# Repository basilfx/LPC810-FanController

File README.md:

# LPC810 Fan Controller
Tiny PID-based fan controller board and firmware, to insert between 3-pin fans.

## Contents
* Eagle schematic and PCB
* Firmware
* PID simulator and monitor

## Eagle

### Bill of Materials
The value of is a pullup resistor for the DS18B20 temperature sensor. While 4.7k is adviced, I use 470 in parasite mode. Higher values did not work for higher temperatures.

| Part | Value  | Device          | Package |
|------|--------|-----------------|---------|
| R1   | 470    | R-EU_R0603      | R0603   |
| R2   | 10k    | R-EU_R0603      | R0603   |
| R3   | 10k    | R-EU_R0603      | R0603   |
| R4   | 10k    | R-EU_R0603      | R0603   |
| C1   | 100nF  | C-EUC0603       | C0603   |
| C2   | 2.2µF  | C-EUC0805       | C0805   |
| C3   | 100nF  | C-EUC0603       | C0603   |
| C4   | 2.2µF  | C-EUC0805       | C0805   |
| Q1   | BSH103 | MOSFET-NCHANNEL | SOT23   |
| U1   | LP2985 | LP2985-33DBVT   | SOT95P  |
| U2   | LPC810 | LPC810M021FN8   | DIP8    |

### Board render
The board measures 0.45x0.95 inch. Below a render of the top and bottom.

## Firmware
The firmware can be found in the `firmware/` folder. It compiles fine with the [GCC ARM Embedded](https://launchpad.net/gcc-arm-embedded) toolchain. Just run `make`.

## Contrib
In the `contrib` folder contains some tools to test the PID controller. First, run `python setup.py build_ext --inplace` to build a Python wrapper for the exact same PID controller in the firmware. This requires Cython to be available.

## License
See the `LICENSE` file (MIT license).

This software makes use of other software. Please see `firmware/README.md` for more information.

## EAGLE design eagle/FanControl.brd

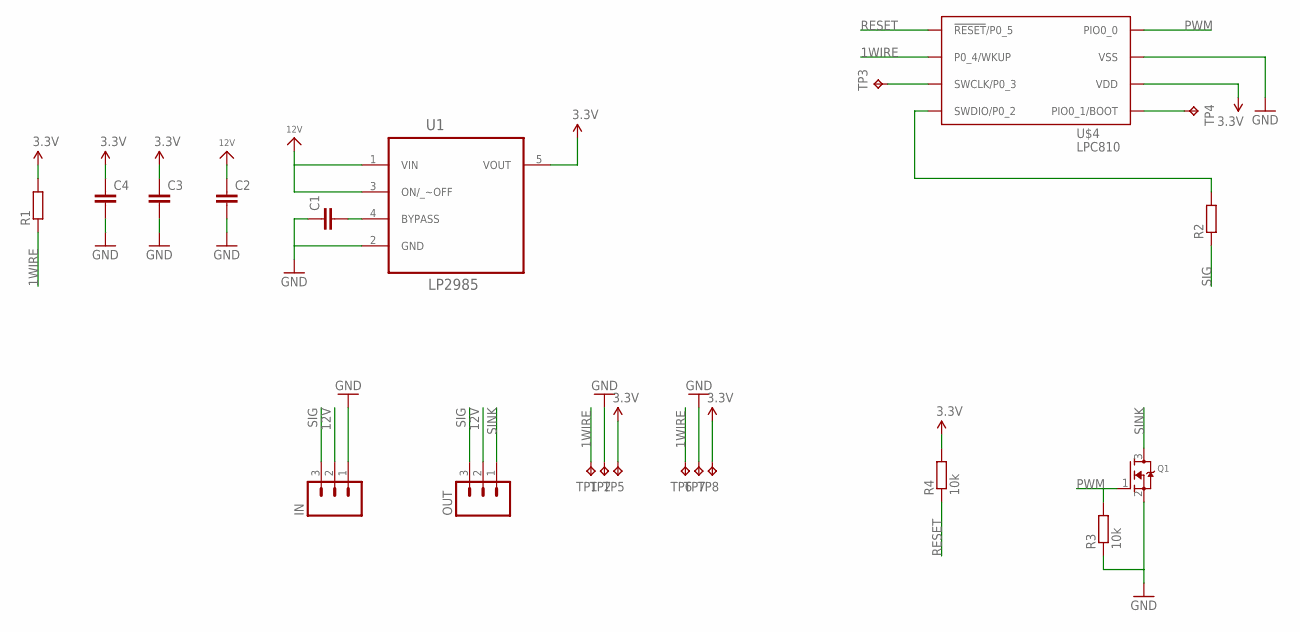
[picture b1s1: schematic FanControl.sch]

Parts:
C1, C3: C-EUC0603; C0603
C2, C4: C-EUC0805; C0805
IN: M03PTH; 1X03
OUT: M03PTH; 1X03
Q1: MOSFET-NREFLOW; SOT23
R1, R2: R-EU_R0603; R0603
R3, R4: 10k; R0603
TP1, TP2, TP3, TP4, TP5, TP6, TP7, TP8: TPB1,27; B1,27
U1: LP2985; SOT95P280X145-5N
U$4: LPC810; DIP8

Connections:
1WIRE: R1.1, TP1.TP, TP6.TP, U$4.P$2 (P0_4/WKUP)
3.3V: C3.1, C4.1, R1.2, R4.2, TP5.TP, TP8.TP, U1.5 (VOUT), U$4.P$6 (VDD)
12V: C2.1, IN.2, OUT.2, U1.1 (VIN), U1.3 (ON/_~OFF)
GND: C1.1, C2.2, C3.2, C4.2, IN.1, Q1.2 (S), R3.1, TP2.TP, TP7.TP, U1.2 (GND), U$4.P$7 (VSS)
unnamed: C1.2, U1.4 (BYPASS)
unnamed: R2.2, U$4.P$4 (SWDIO/P0_2)
unnamed: TP3.TP, U$4.P$3 (SWCLK/P0_3)
unnamed: TP4.TP, U$4.P$5 (PIO0_1/BOOT)
PWM: Q1.1 (G), R3.2, U$4.P$8 (PIO0_0)
RESET: R4.1, U$4.P$1 (!RESET!/P0_5)
SIG: IN.3, OUT.3, R2.1
SINK: OUT.1, Q1.3 (D)

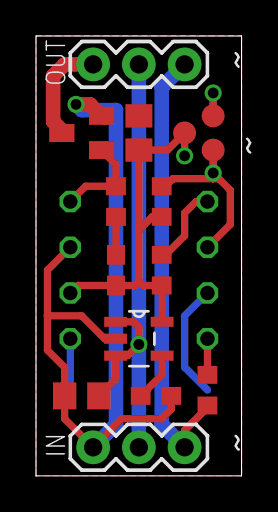
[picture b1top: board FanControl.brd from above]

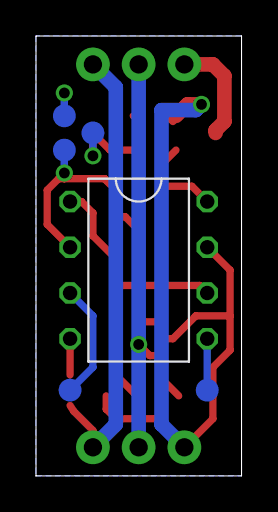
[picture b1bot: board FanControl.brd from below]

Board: 2 copper layers, 11.4 x 24.4 mm, 21 parts (6 on the bottom side), 12 nets.

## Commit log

2014-12-08 Added gitignore
2014-12-08 Second version of schematics and PCB
2014-12-08 Gitignore per directory.
2014-12-08 Initial firmware version
2014-12-08 Ignore eagle temp files.
2014-12-08 Added contributions.
2014-12-09 Parameters to config.h
2014-12-09 Added docs.
2014-12-09 Corrected paths.
2014-12-09 Updated URLs.
2014-12-09 Updated links.
2014-12-09 Lower temperature.
2014-12-09 Updated README with a BOM.
2014-12-09 Increase stack size for printf magic.
2014-12-09 Add support for multiple sensors controlling one fan.
2014-12-09 Monitor multiple sensors.
2014-12-10 Added extra pads for another 1-Wire device on the bottom layer.
2014-12-10 Initialize to zero.
2014-12-10 Minor changes.
2014-12-10 Reimplemented PID controller to account for better value ranges.
2014-12-10 Updates simulator and plotter.
2014-12-11 Better parameters
2015-02-04 Shouldn't be in vcs

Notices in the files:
parts and their libraries:
SparkFun-Connectors: Licensing: Creative Commons ShareAlike 4.0 International - https://creativecommons.org/licenses/by-sa/4.0
microbuilder: This work is placed in the public domain, and may be freely used for commercial and non-commercial work with the following conditions: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
